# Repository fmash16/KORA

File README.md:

# KORA
An Ergonomic Orthogonal Split keyboard with high modularity

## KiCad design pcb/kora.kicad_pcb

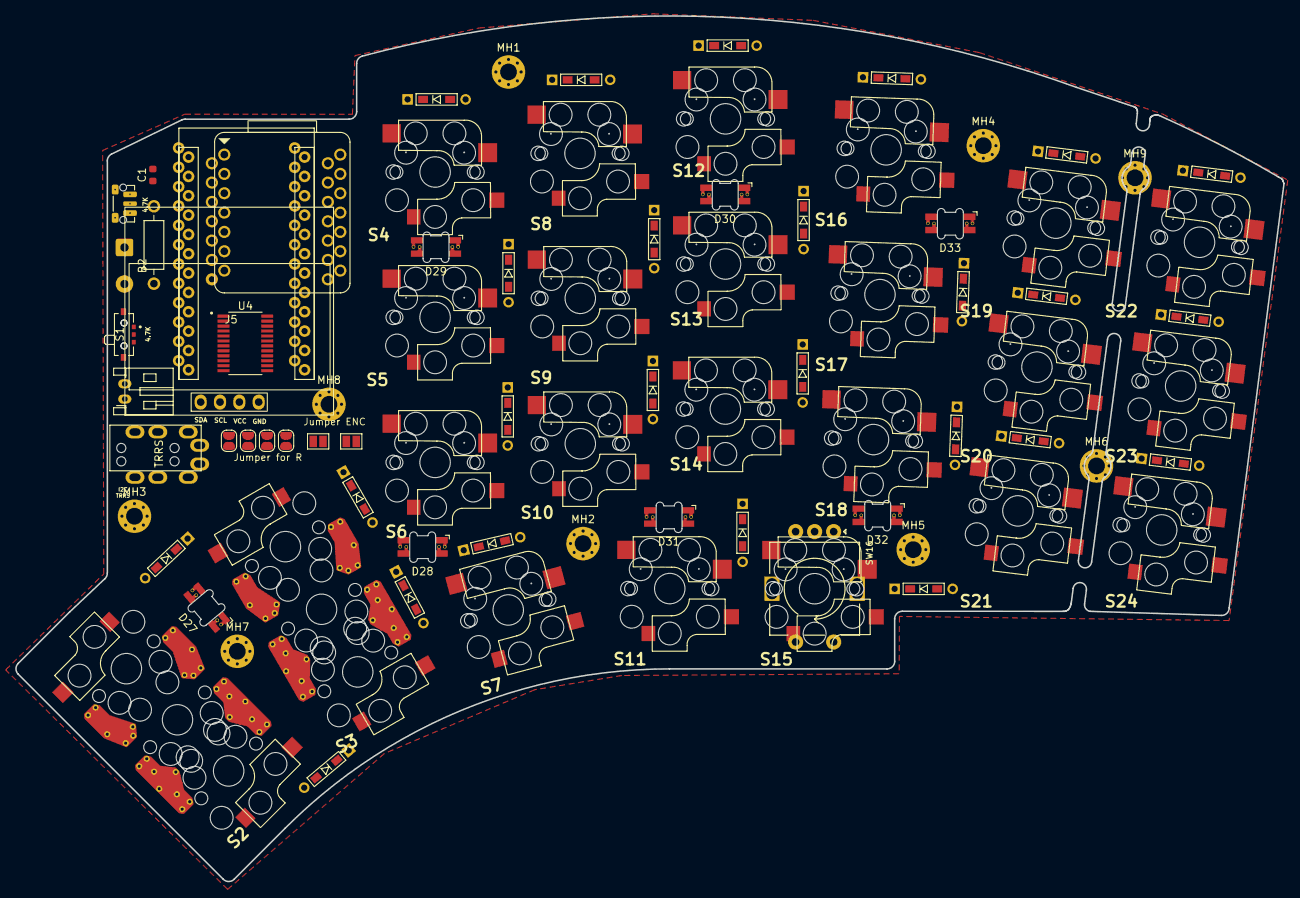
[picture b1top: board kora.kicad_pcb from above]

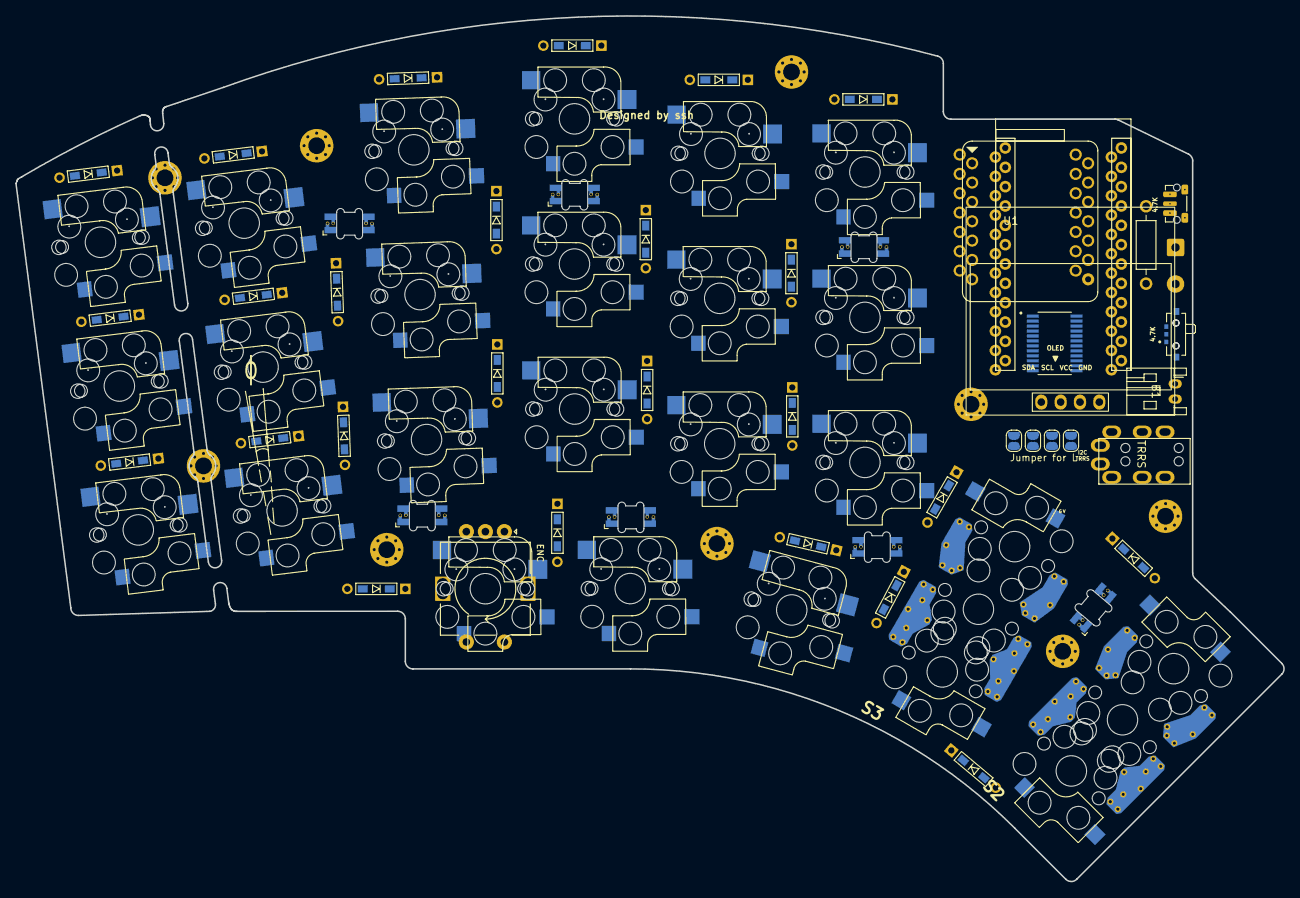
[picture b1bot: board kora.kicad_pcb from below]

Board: 2 copper layers, 166.5 x 113.7 mm, 86 parts (5 on the bottom side), 61 nets, no tracks yet.

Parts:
B1: JST Battery; JST_PH_reversible
B2: Battery Pads; SolderWire-0.5sqmm_1x02_P4.8mm_D0.9mm_OD2.3mm
C1: 100n; SMD-0603
D1, D2, D3, D4, D5, D6, D7, D8, D9, D10, D11, D12, D13, D14, D15, D16, D17, D18, D19, D20, D21, D22, D23, D24, D25: 1N4148; D3_TH_SMD
D27, D28, D29, D30, D31, D32, D33: SK6812Mini-e; SK6812_mini_e_flipable
J5: OLED-128x64; SSD1306_128x64OLED
JP1, JP2, JP3, JP4, JP5, JP6, JP7, JP8: Jumper_2_Open; SolderJumper-2_P1.3mm_Open_RoundedPad1.0x1.5mm
JP9, JP10: Jumper_2_Open; SolderJumper-2_P1.3mm_Open_Pad1.0x1.5mm
MH1, MH2, MH3, MH4, MH5, MH6, MH7, MH8, MH9: MOUNT_HOLE; MountingHole_2.2mm_M2_Pad_Via
R1: 4.7K; RESISTOR
RSW1: SW_Push; SW_Push_1P1T-MP_NO_Horizontal_Alps_SKRTLAE010_both_sides
S1: EG1218; RevSlideSwitch
S2, S3: SW; MX__CHOC_KAILH_SOCKET_2U_2X1U
S4, S5, S6, S7, S8, S9, S10, S11, S12, S13, S14, S15, S16, S17, S18, S19, S20, S21, S22, S23, S24: SW; MX_Choc_Hotswap_Mod
SW16: RotaryEncoder_Switch; MX-1U-EC11_Switch
U1: XIAO-BLE
U2: ProMicro; ProMicro_rev2
U3: TRRS; MJ-4PP-9
U4: TCA9555PWR

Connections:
+3V3: C1.1, D27.1 (VDD), D28.1 (VDD), D29.1 (VDD), D30.1 (VDD), D31.1 (VDD), D32.1 (VDD), D33.1 (VDD), JP2.2 (B), JP7.2 (B), R1.2, U1.12 (3V3), U2.21 (VCC), U3.T, U4.24 (VCC)
BAT+: S1.3, U2.24 (RAW)
COL 0: S2.A, S2.C, U1.7 (PB08_A6_D6_TX), U2.18 (F6/A1), U4.4 (P00)
COL 1: S3.A, S4.1, S5.1, S6.1, U1.11 (PA6_A10_D10_MOSI), U2.17 (F7/A0), U4.5 (P01)
COL 2: S3.C, S8.1, S9.1, S10.1, U1.10 (PA5_A9_D9_MISO), U2.16 (B1/15), U4.6 (P02)
COL 3: S7.1, S12.1, S13.1, S14.1, U1.9 (PA7_A8_D8_SCK), U2.15 (B3/14), U4.7 (P03)
COL 4: S11.1, S16.1, S17.1, S18.1, U1.8 (PB09_A7_D7_RX), U2.14 (B2/16), U4.8 (P04)
COL 5: S15.1, S19.1, S20.1, S21.1, SW16.S1, U2.13 (B6/10), U4.9 (P05)
COL 6: S22.1, S23.1, S24.1, U2.12 (9/B5), U4.10 (P06)
ENC_A: JP9.2 (B), SW16.A, U2.20 (F4/A3)
ENC_B: JP10.2 (B), SW16.B, U2.19 (F5/A2)
GND: B1.2, B2.2 (-), C1.2, D27.3 (VSS), D28.3 (VSS), D29.3 (VSS), D30.3 (VSS), D32.3 (VSS), D33.3 (VSS), JP1.2 (B), JP8.2 (B), MH1.1, MH2.1, MH3.1, MH4.1, MH5.1, MH6.1, MH7.1, MH8.1, MH9.1, RSW1.1, SW16.C, U1.13 (GND), U2.3 (GND), U2.4 (GND), U2.23 (GND), U3.S, U4.12 (GND)
unnamed: B1.1, B2.1 (+), S1.2
unnamed: D1.2 (A), S5.2
unnamed: D1.1 (K), D2.1 (K), D3.1 (K), D4.1 (K), D6.1 (K), D7.1 (K)
unnamed: D2.2 (A), S9.2
unnamed: D3.2 (A), S13.2
unnamed: D4.2 (A), S17.2
unnamed: D5.2 (A), S4.2
unnamed: D6.2 (A), S20.2
unnamed: D7.2 (A), S23.2
unnamed: D8.2 (A), S6.2
unnamed: D9.2 (A), S8.2
unnamed: D10.2 (A), S10.2
unnamed: D11.2 (A), S14.2
unnamed: D12.2 (A), S18.2
unnamed: D13.2 (A), S12.2
unnamed: D14.2 (A), S21.2
unnamed: D15.2 (A), S24.2
unnamed: D16.2 (A), S2.B
unnamed: D17.2 (A), S16.2
unnamed: D18.2 (A), S3.D
unnamed: D19.2 (A), S7.2
unnamed: D20.2 (A), S19.2
unnamed: D21.2 (A), S11.2
unnamed: D22.2 (A), S15.2
unnamed: D23.2 (A), S22.2
unnamed: D24.2 (A), S3.B
unnamed: D25.2 (A), S2.D
unnamed: D27.2 (DOUT), D28.4 (DIN)
unnamed: D28.2 (DOUT), D29.4 (DIN)
unnamed: D29.2 (DOUT), D30.4 (DIN)
unnamed: D30.2 (DOUT), D31.4 (DIN)
unnamed: D31.2 (DOUT), D32.4 (DIN)
unnamed: D32.2 (DOUT), D33.4 (DIN)
unnamed: J5.1 (GND), JP1.1 (A), JP5.1 (A)
unnamed: J5.3 (SCL), JP3.1 (A), JP7.1 (A)
unnamed: J5.4 (SDA), JP4.1 (A), JP8.1 (A)
unnamed: J5.2 (VCC), JP2.1 (A), JP6.1 (A)
unnamed: U4.2 (A1), U4.3 (A2)
unnamed: R1.1, U4.1 (~INT)
RESET: RSW1.2, U2.22 (RST)
RGB: D27.4 (DIN), U2.1 (TX0/D3)
ROW 0: D5.1 (K), D9.1 (K), D13.1 (K), D17.1 (K), D20.1 (K), D23.1 (K), U1.1 (PA02_A0_D0), U2.8 (5/C6)
ROW 1: U1.2 (PA4_A1_D1), U2.9 (6/D7)
ROW 2: D8.1 (K), D10.1 (K), D11.1 (K), D12.1 (K), D14.1 (K), D15.1 (K), D16.1 (K), U1.3 (PA10_A2_D2), U2.10 (7/E6)
ROW 3: D18.1 (K), D19.1 (K), D21.1 (K), D22.1 (K), D24.1 (K), D25.1 (K), SW16.S2, U1.4 (PA11_A3_D3), U2.11 (8/B4)
RX: U2.7 (4/D4), U3.R1
SCL: JP3.2 (B), JP6.2 (B), JP10.1 (A), U1.6 (PA9_A5_D5_SCL), U2.6 (3/D0/SCL), U4.22 (SCL)
SDA: JP4.2 (B), JP5.2 (B), JP9.1 (A), U1.5 (PA8_A4_D4_SDA), U2.5 (2/D1/SDA), U4.23 (SDA)
TX: U2.2 (RX1/D2), U3.R2
